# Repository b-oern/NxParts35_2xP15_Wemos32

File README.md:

# NxP-35  2xP15 WemosESP32

This repository contains the KiCad PCB design files for a custom ESP32 Wemos32 module carrier board.

Key Features:

 - ESP32 Wemos32 socket for direct module integration
 - Two P15 board-to-board connectors for peripheral expansion and signal routing
 - Onboard step-down converter (5V regulator) for stable supply from higher input voltages
 - Voltage sensing circuit on GPIO39 (IO39) enabling ADC-based supply monitoring
 - Compact PCB layout optimized for modular integration into larger systems

This hardware is intended as a foundation for embedded applications requiring regulated 5V input, expandable connectivity, and real-time power supervision.

---
## See also

 - [nweb:doc](https://pi.bsnx.net/4.0/w/group/118AFDA59CAAB3FA49CA190666FCF396/d/43205) (Restricted Access)

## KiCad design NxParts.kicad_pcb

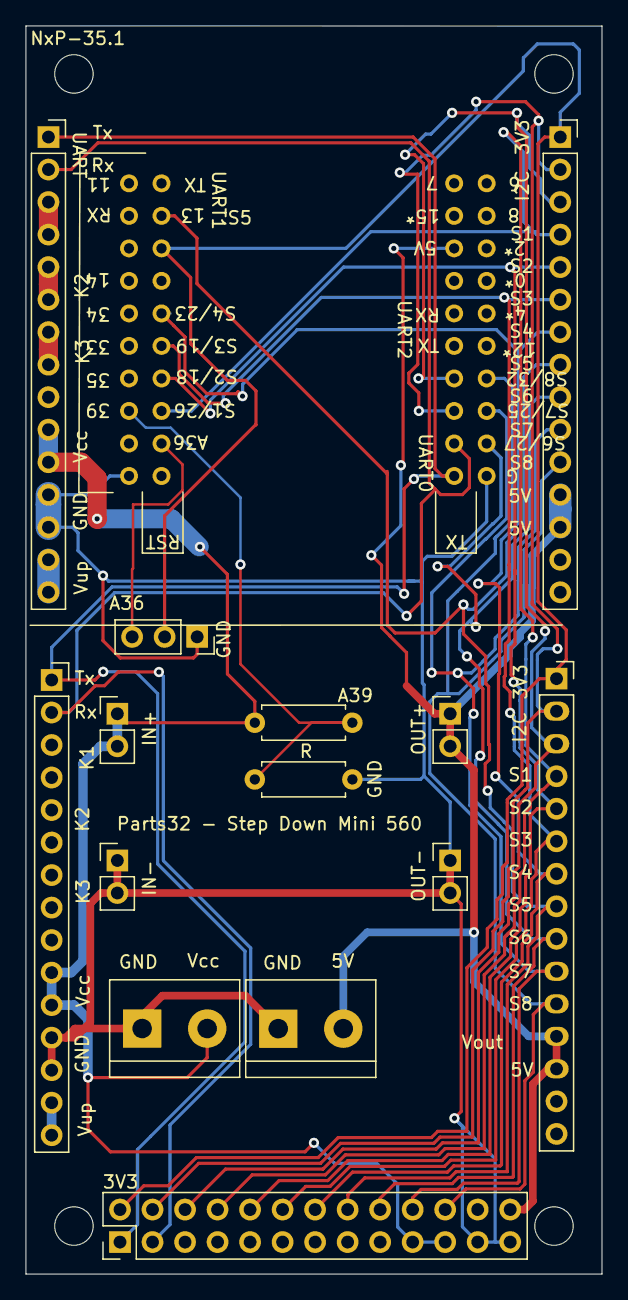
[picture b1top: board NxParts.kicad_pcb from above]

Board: 2 copper layers, 45.0 x 97.5 mm, 8 parts (1 on the bottom side), 16 nets.

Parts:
3V3: P2; PinHeader_2x13_P2.54mm_Vertical
A39: R; R_Axial_DIN0207_L6.3mm_D2.5mm_P7.62mm_Horizontal
IN+: P2; PinHeader_1x02_P2.54mm_Vertical
IN-: P2; PinHeader_1x02_P2.54mm_Vertical
OUT+: P2; PinHeader_1x02_P2.54mm_Vertical
OUT-: P2; PinHeader_1x02_P2.54mm_Vertical
R: R; R_Axial_DIN0207_L6.3mm_D2.5mm_P7.62mm_Horizontal
U1: mini_esp32; ESP32_mini

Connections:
+3V3: 3V3.2, U1.16
+5V: 3V3.24, 3V3.26, OUT+.1, OUT+.2, U1.35
+24V: 3V3.19, 3V3.21, A39.2, IN+.1, IN+.2
D0: 3V3.8, U1.6
D5: 3V3.10, U1.8
D6: 3V3.12, U1.10
D7: 3V3.14, U1.12
D8: 3V3.16, U1.18
GND: 3V3.23, 3V3.25, IN-.1, IN-.2, OUT-.1, OUT-.2, R.1, U1.1, U1.22, U1.33
Io25: 3V3.20, U1.26
Io27: 3V3.18, U1.24
Io32: 3V3.22, U1.28
RX: 3V3.3, U1.17, U1.23, U1.31
SCL: 3V3.4, U1.25
SDA: 3V3.6, U1.27
TX: 3V3.1, U1.20, U1.21, U1.29

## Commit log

2025-08-24 init
